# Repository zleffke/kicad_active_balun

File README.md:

# kicad_active_balun
Active Balun Designs for HF Reception.  Based on Long Wavelength Array designs.

## References

- [Reeve Observatory - Long Wavelength Array Active Crossed-Dipole Antenna](http://www.reeve.com/RadioScience/Antennas/ActiveCrossed-Dipole/LWA_Antenna.htm)
- [Long Wavelength Array (LWA) Memo Series](https://www.faculty.ece.vt.edu/swe/lwa/)

### active_balun_v1, rev-, 20200615
This design is heavily based on the Long Wavelength Array (LWA) Front End Electronics (FEE), version 1.7.  More information about the LWA FEE v1.7 can be found at the above references.

Major design differences include:
- updated parts. Some of the components are not avaialble on digikey, minor difference.
- 8V regulator instead of 12V regulator.  GALI-74+ and GALI-6+ bias circuitry adjusted accordingly.
- Biasing set for low noise, high OIP3 based on datasheets for GALI devices.
- Not using the HX62A 180 deg hybrid (too expensive).  Instead using Mini Circuits 2:1 RF transformer / Balun.  Planning to Use ADT2-1T.  LWA documentation does include comparison of HX62A with ADT2-1T-1P, however the lowend of this balun is 8 MHz.  ADT2-1T low end is less than 1 MHz.  However the Polarity Mark of the primary coil is reversed. May try other cheaper 180 deg hybrids from Mini Circuits in future versions.
- Provided multiple solder jumpers for various experiments.  first is alternating the ADT2-1T unbalanced output between pins 1 and 3. Jumper allows grounding of the other pin.
- Filter options, selected via solder jumper:
    - Default configuration is no filter, direct path from Balun to GALI-6 input.
    - LPF: Cutoff frequency = 50 MHz. -30dB at 100MHz from Qucs simulation.
    - BPF: low cut = 1 MHz, high cut = 50 MHz.  -30dB @100 MHz from Qucs simulation.

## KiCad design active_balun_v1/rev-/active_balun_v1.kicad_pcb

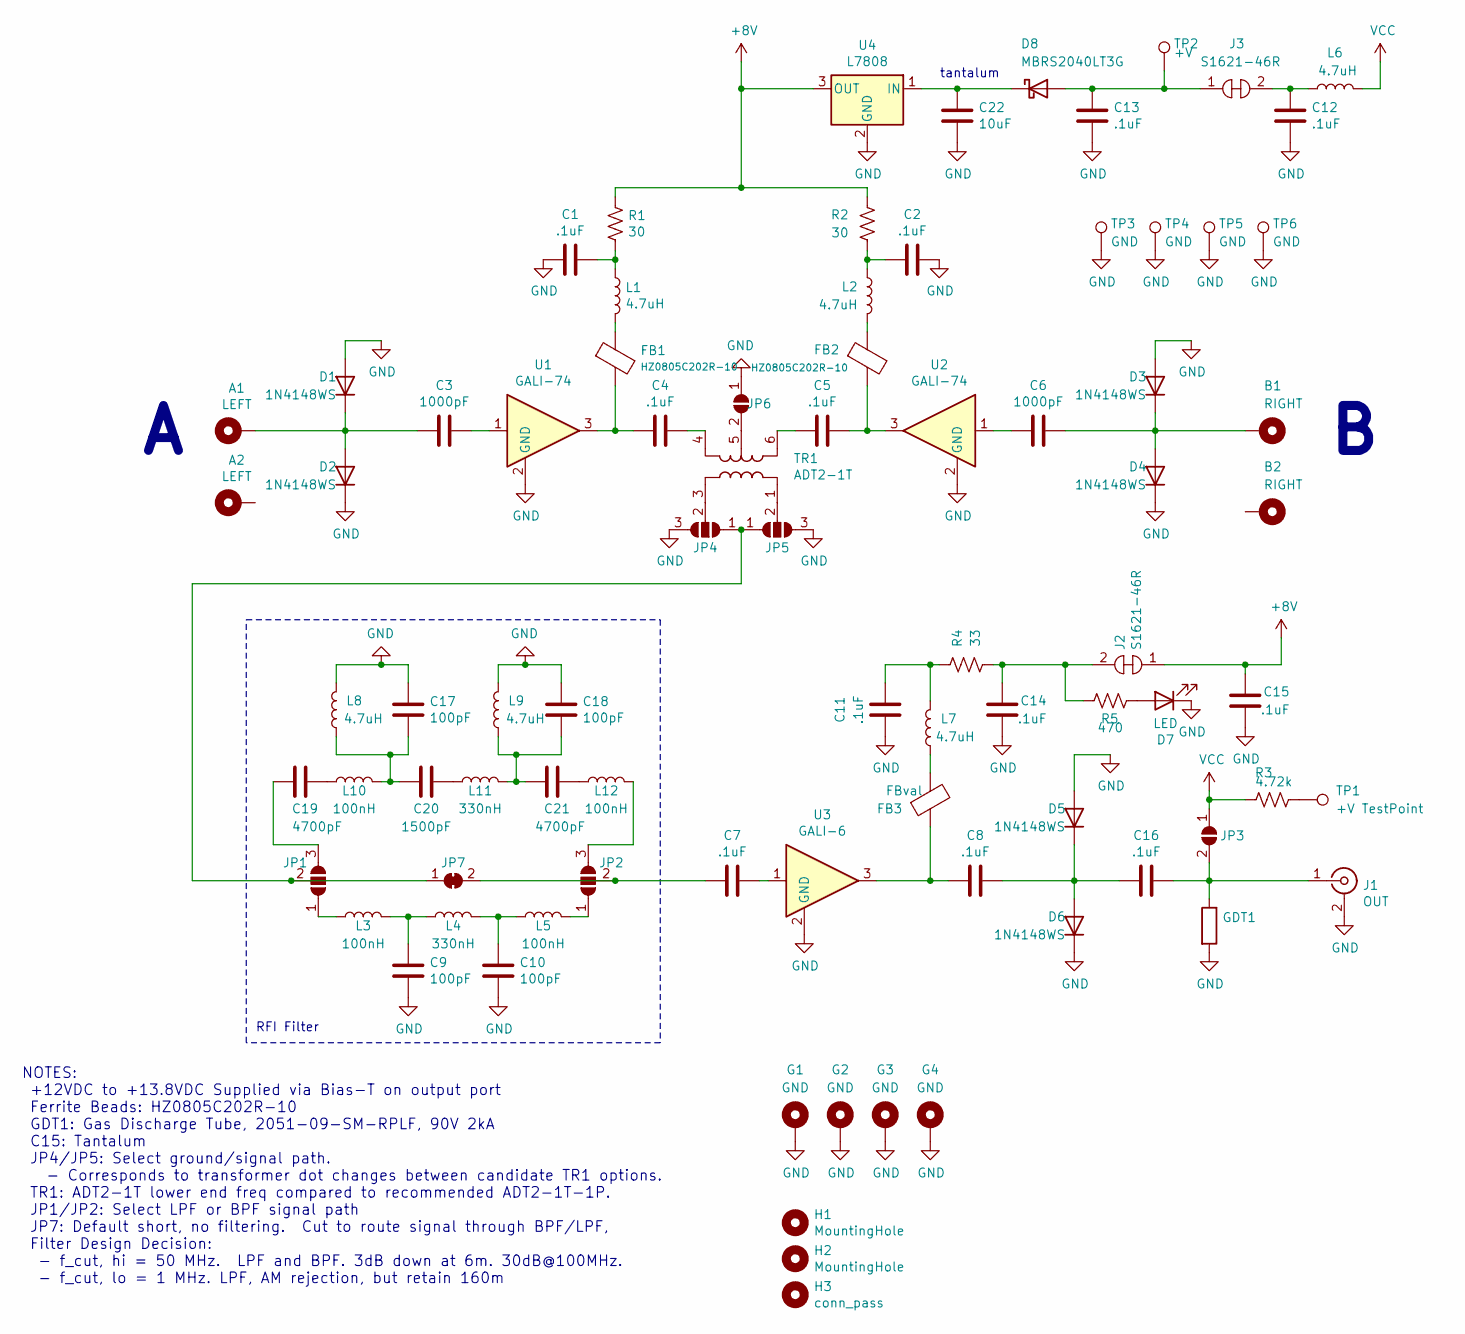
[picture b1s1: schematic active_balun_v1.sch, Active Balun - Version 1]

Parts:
A1, A2: LEFT; MountingHole_3.7mm_Pad_Via
B1, B2: RIGHT; MountingHole_3.7mm_Pad_Via
C1, C2, C4, C5, C7, C8, C11, C12, C13, C14, C15, C16: .1uF; 0805
C3, C6: 1000pF; 0805
C9, C10, C17, C18: 100pF; 0805
C19, C21: 4700pF; 0805
C20: 1500pF; 0805
C22: 10uF; CP_EIA-3528-15_AVX-H
D1, D2, D3, D4, D5, D6: 1N4148WS; D_SOD-323
D7: LED; LED_0805_2012Metric
D8: MBRS2040LT3G; D_SMB_Handsoldering
FB1, FB2: HZ0805C202R-10; 0805
FB3: FBval; 0805
G1, G2, G3, G4: GND; MountingHole_3.2mm_M3_Pad_Via
GDT1: L_1812_4532Metric
H1, H2: MountingHole; MountingHole_3.2mm_M3
H3: conn_pass; MountingHole_3.2mm_M3
J1: OUT; SMA_Amphenol_132134_Vertical
J2, J3: S1621-46R; Jumper_Tin_P10.9mm; MPN S1621-46R; Digi-Key_PN 952-1474-1-ND
JP1, JP2, JP4, JP5: SolderJumper-3_P1.3mm_Open_RoundedPad1.0x1.5mm
JP3, JP6: SolderJumper-2_P1.3mm_Open_RoundedPad1.0x1.5mm
JP7: NetTie-2_SMD_Pad0.5mm
L1, L2, L7, L8, L9: 4.7uH; 0805
L3, L5, L10, L12: 100nH; 0805
L4, L11: 330nH; 0805
L6: 4.7uH; L_1008_2520Metric
R1, R2: 30; R_1206_3216Metric
R3: 4.72k; 0805
R4: 33; R_1206_3216Metric
R5: 470; 0805
TP1: +V TestPoint; TestPoint_Pad_D2.0mm
TP2: +V; TestPoint_Pad_2.5x2.5mm
TP3, TP4, TP5, TP6: GND; TestPoint_Pad_2.5x2.5mm
TR1: ADT2-1T; Mini-Circuits_CD542_H2.84mm
U1, U2: GALI-74; SOT-89-3
U3: GALI-6; SOT-89-3
U4: L7808; TO-263-2

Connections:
+8V: C15.2, J2.1, R1.1, R2.1, U4.3 (OUT)
GND: C1.2, C2.1, C9.1, C10.1, C11.2, C12.1, C13.1, C14.1, C15.1, C17.2, C18.2, C22.1, D1.2 (A), D2.1 (K), D3.2 (A), D4.1 (K), D5.2 (A), D6.1 (K), D7.1 (K), G1.1, G2.1, G3.1, G4.1, GDT1.2, J1.2 (Ext), JP4.3 (B), JP5.3 (B), JP6.1 (A), L8.2, L9.2, TP3.1, TP4.1, TP5.1, TP6.1, U1.2 (GND), U2.2 (GND), U3.2 (GND), U4.2 (GND)
unnamed: A1.1, C3.2, D1.1 (K), D2.2 (A)
unnamed: B1.1, C6.1, D3.1 (K), D4.2 (A)
unnamed: C1.1, L1.1, R1.2
unnamed: C2.2, L2.1, R2.2
unnamed: C3.1, U1.1
unnamed: C4.1, TR1.4
unnamed: C4.2, FB1.2, U1.3
unnamed: C5.1, FB2.2, U2.3
unnamed: C5.2, TR1.6
unnamed: C6.2, U2.1
unnamed: C7.1, U3.1
unnamed: C7.2, JP2.2 (C), JP7.2 (B)
unnamed: C8.1, FB3.1, U3.3
unnamed: C9.2, L3.2, L4.1
unnamed: C10.2, L4.2, L5.1
unnamed: C11.1, L7.2, R4.2
unnamed: C12.2, J3.2, L6.2
unnamed: C13.2, D8.2 (A), J3.1, TP2.1
unnamed: C14.2, J2.2, R4.1, R5.1
unnamed: C8.2, C16.1, D5.1 (K), D6.2 (A)
unnamed: C16.2, GDT1.1, J1.1 (In), JP3.2 (B)
unnamed: C17.1, C20.1, L8.1, L10.2
unnamed: C18.1, C21.1, L9.1, L11.2
unnamed: C19.1, JP1.3 (B)
unnamed: C19.2, L10.1
unnamed: C20.2, L11.1
unnamed: C21.2, L12.1
unnamed: C22.2, D8.1 (K), U4.1 (IN)
unnamed: D7.2 (A), R5.2
unnamed: FB1.1, L1.2
unnamed: FB2.1, L2.2
unnamed: FB3.2, L7.1
unnamed: JP1.1 (A), L3.1
unnamed: JP1.2 (C), JP4.1 (A), JP5.1 (A), JP7.1 (A)
unnamed: JP2.1 (A), L5.2
unnamed: JP2.3 (B), L12.2
unnamed: JP4.2 (C), TR1.3
unnamed: JP5.2 (C), TR1.1
unnamed: JP6.2 (B), TR1.5
unnamed: R3.1, TP1.1
VCC: JP3.1 (A), L6.1, R3.2

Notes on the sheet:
NOTES: +12VDC to +13.8VDC Supplied via Bias-T on output port Ferrite Beads: HZ0805C202R-10 GDT1: Gas Discharge Tube, 2051-09-SM-RPLF, 90V 2kA C15: Tantalum JP4/JP5: Select ground/signal path. - Corresponds to transformer dot changes between candidate TR1 options. TR1: ADT2-1T lower end freq compare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
tantalum
RFI Filter

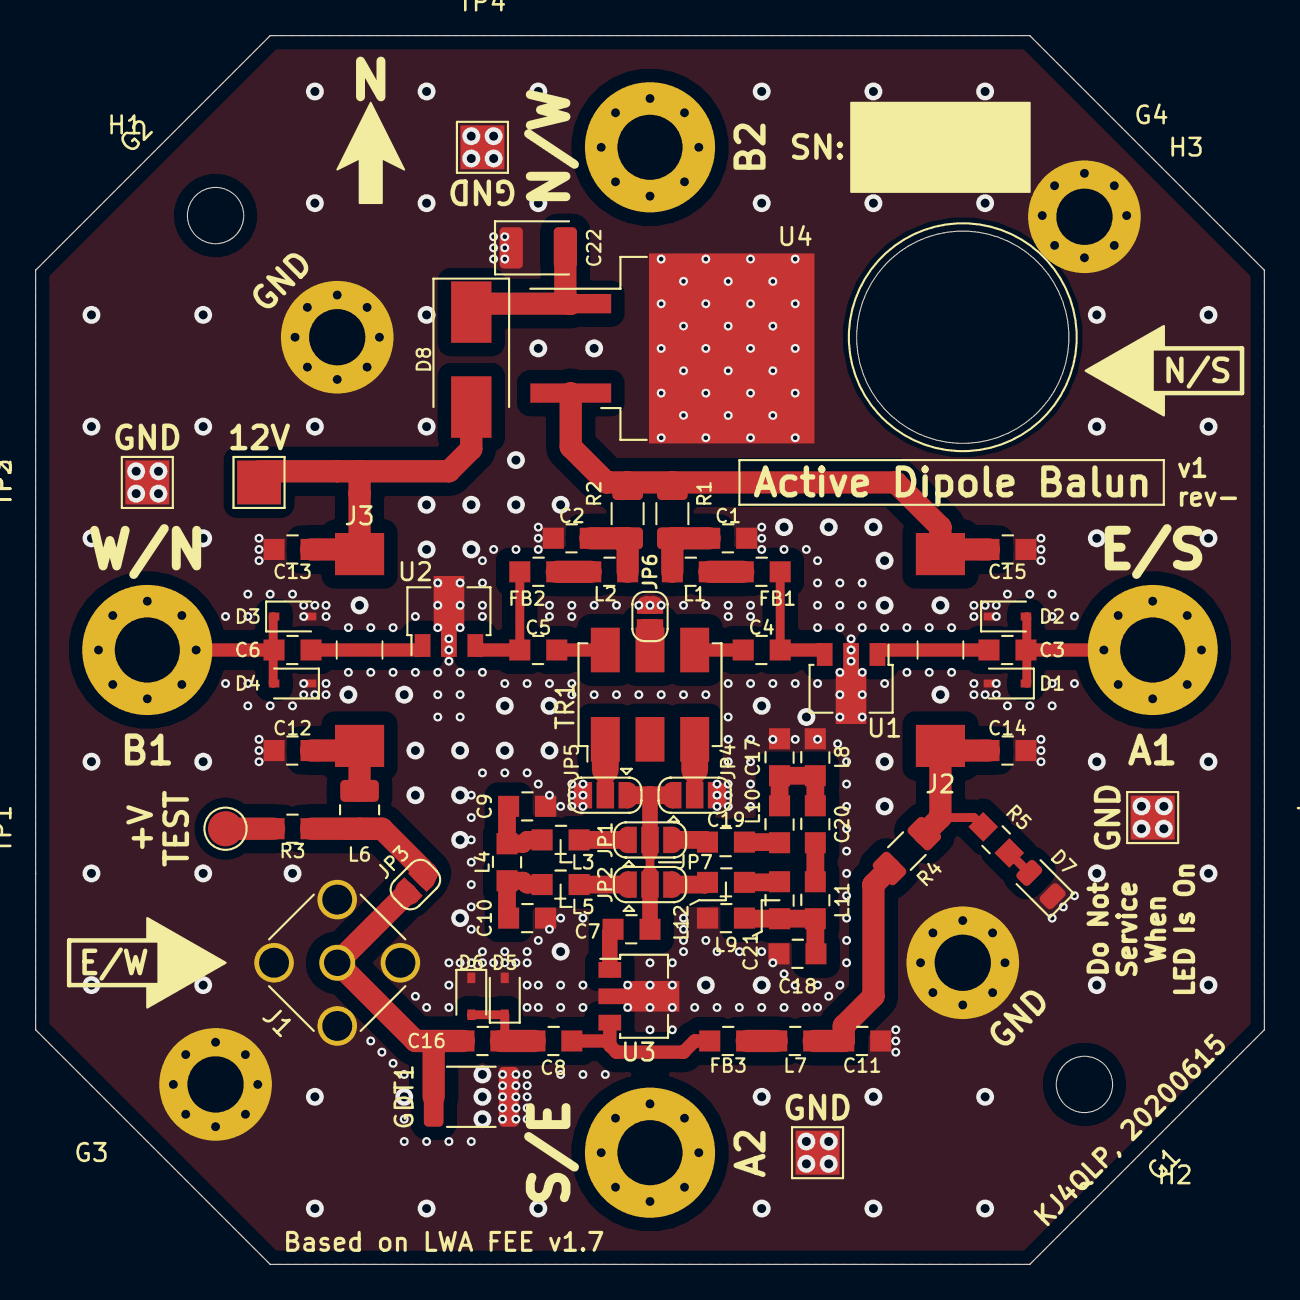
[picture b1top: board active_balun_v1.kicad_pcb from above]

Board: 2 copper layers, 69.8 x 69.8 mm, 83 parts (0 on the bottom side), 43 nets.

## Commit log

2020-06-15 mass commit of completed v1, rev1. This commit submitted to Osh Park, 20200615.
2020-06-15 qucs designs. lpf and bpf designs for active dipole balun.
2020-06-15 added images from osh park
2020-08-22 added documentation and rf measurement data.....its a big repo now...
2020-09-05 adding presentation for TAPR-DCC 2020.

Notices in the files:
active_balun_v1/rev-/active_balun_v1.kicad_pcb:
License: CC BY 4.0
active_balun_v1/rev-/active_balun_v1.sch:
creativecommons.org/licenses/by/4.0
